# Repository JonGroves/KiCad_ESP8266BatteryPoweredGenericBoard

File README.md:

A generic ESP8266 board that allows for standard features, including programming, programming and reset buttons, USB connection (Power only), and breakout of pins.  ESP8266 is on it's own breakout board, and wide lcd screen breakout is provided for any size LCD (up to 24 pin spacings).

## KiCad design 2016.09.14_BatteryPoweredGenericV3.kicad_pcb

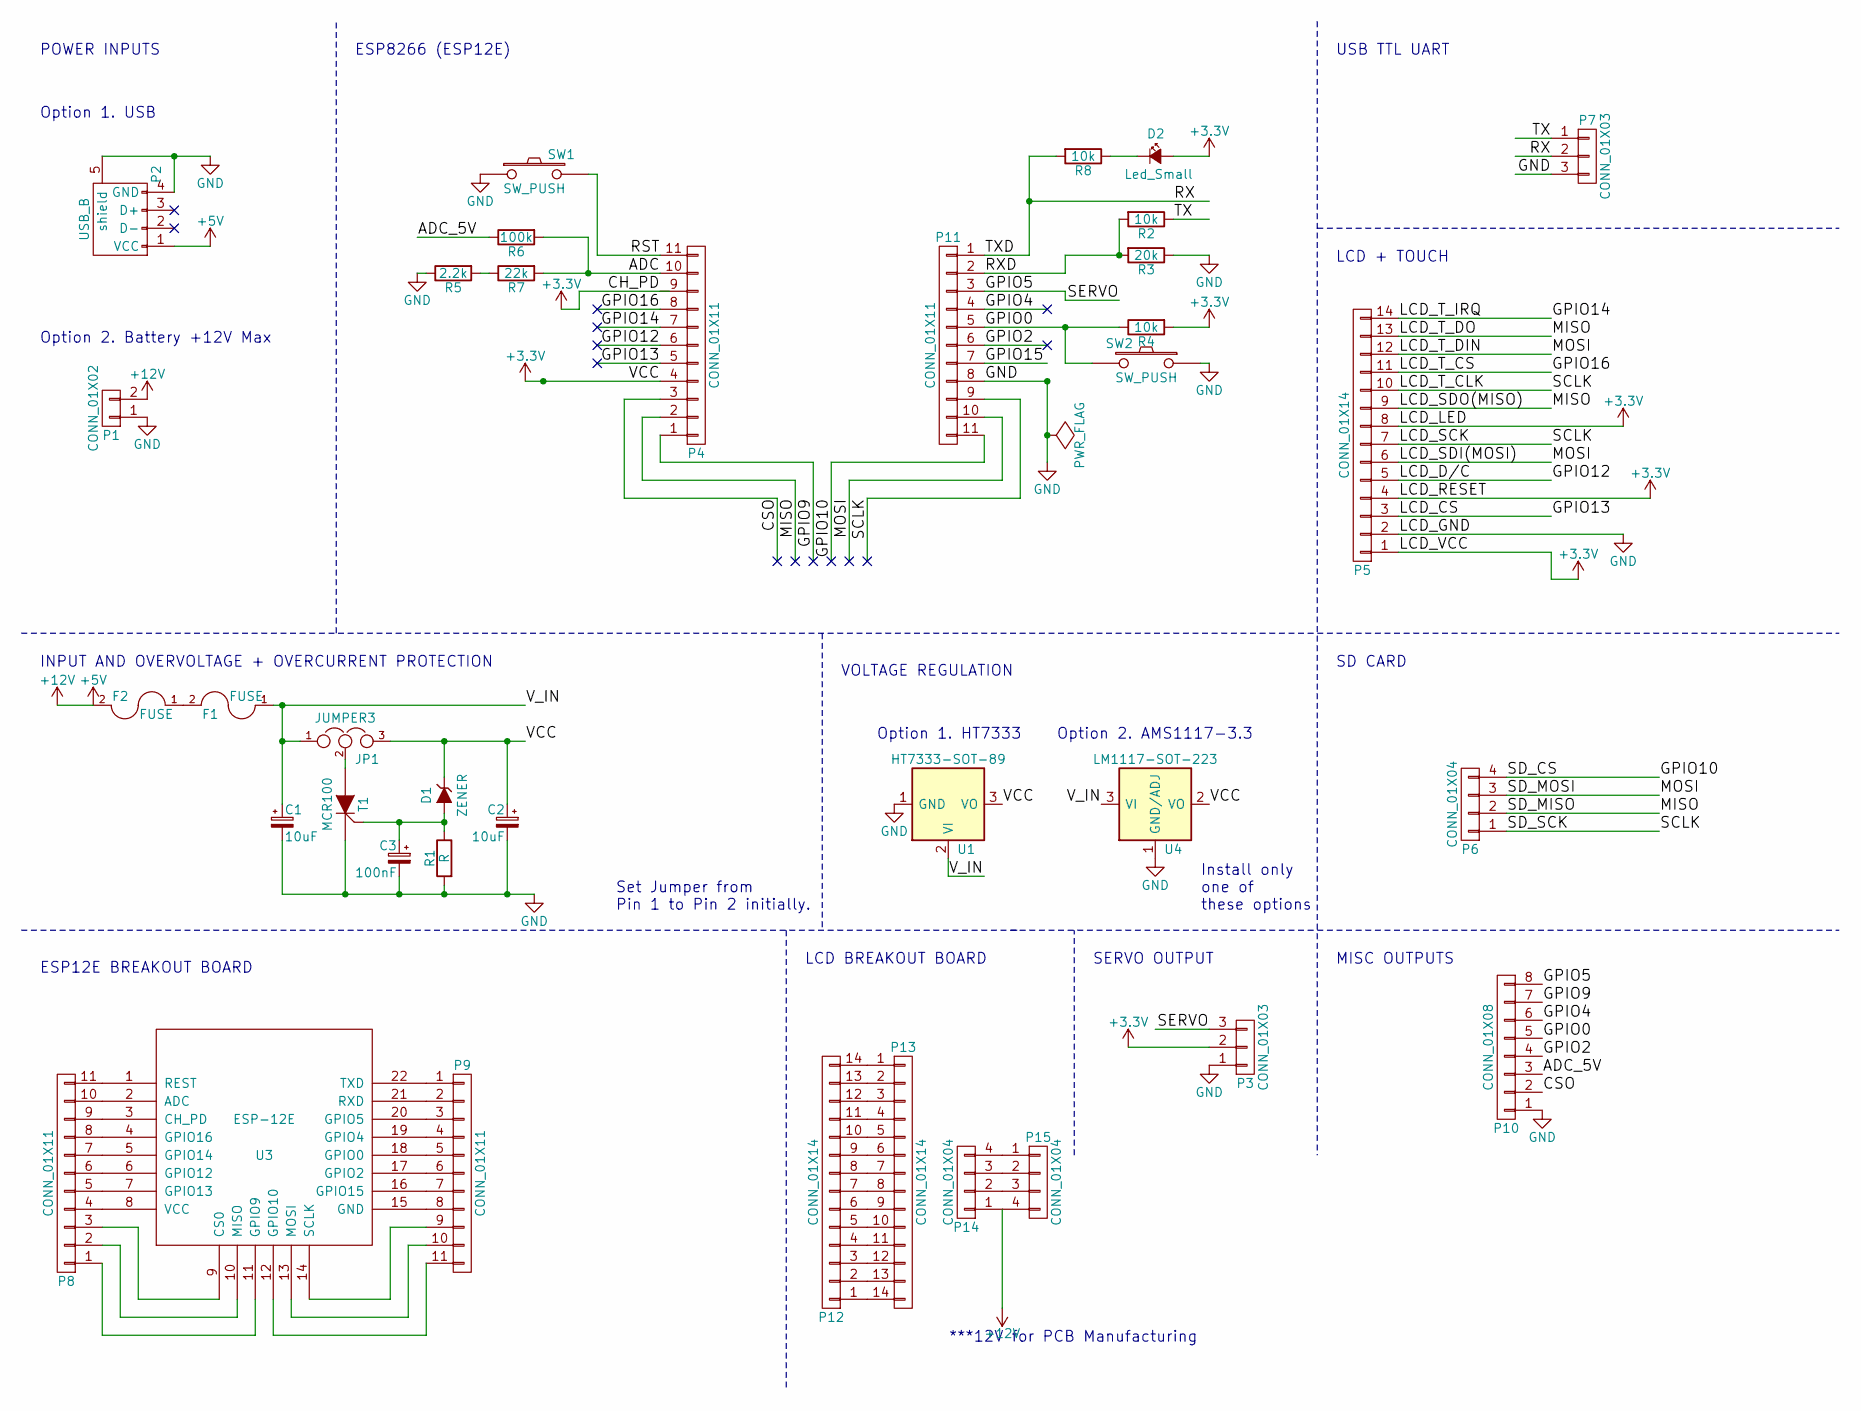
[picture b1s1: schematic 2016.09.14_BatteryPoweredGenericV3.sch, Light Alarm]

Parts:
C1, C2: 10uF; R_0805_HandSoldering
C3: 100nF; R_0805_HandSoldering
D1: ZENER; SOD-123
D2: Led_Small; LED_0603
F1: FUSE; R_1812_HandSoldering
F2: FUSE; Fuseholder5x20_horiz_open_Schurter_0031_8201
JP1: JUMPER3; R_1206_Junction
P1: CONN_01X02; Socket_Strip_Straight_1x02
P2: USB_B; USB_Mini-B
P3, P7: CONN_01X03; Socket_Strip_Straight_1x03
P4, P11: CONN_01X11; Socket_Strip_Straight_1x11
P5, P12: CONN_01X14; Socket_Strip_Straight_1x14
P6, P15: CONN_01X04; Socket_Strip_Straight_1x04
P8, P9: CONN_01X11; Pin_Header_Straight_1x11
P10: CONN_01X08; Socket_Strip_Straight_1x08
P13: CONN_01X14; Pin_Header_Straight_1x14
P14: CONN_01X04; Pin_Header_Straight_1x04
R1: R; R_0805_HandSoldering
R2, R4, R8: 10k; R_0805_HandSoldering
R3: 20k; R_0805_HandSoldering
R5: 2.2k; R_0805_HandSoldering
R6: 100k; R_0805_HandSoldering
R7: 22k; R_0805_HandSoldering
SW1, SW2: SW_PUSH; SW_SPST_EVPBF
T1: MCR100; TO-92_Inline_Narrow_Oval
U1: HT7333-SOT-89; SOT89-3_Housing_Handsoldering
U3: ESP-12E; Esp8266_PinsOnly
U4: LM1117-SOT-223; SOT-223

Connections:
+3V3: C2.1, D1.1 (K), D2.2 (A), JP1.3, P3.2, P4.4, P4.9, P5.1, P5.4, P5.8, R4.2, U1.3 (VO), U4.2 (VO)
+12V: F2.2, P1.2, P2.1 (VCC), P14.1, P15.4
/ADC: P4.10, R6.2, R7.2
/ADC_5V: P10.3, R6.1
/CSO: P4.3, P10.2
/GPIO0: P10.5, P11.5, R4.1, SW2.2
/GPIO2: P10.4, P11.6
/GPIO4: P10.6, P11.4
/GPIO5: P3.3, P10.8, P11.3
/GPIO9: P4.1, P10.7
/GPIO10: P6.4, P11.11
/GPIO12: P4.6, P5.5
/GPIO13: P4.5, P5.3
/GPIO14: P4.7, P5.14
/GPIO16: P4.8, P5.11
/LCD_SCK: P5.7, P5.10, P6.1, P11.9
/LCD_SDI(MOSI): P5.6, P5.12, P6.3, P11.10
/LCD_SDO(MISO): P4.2, P5.9, P5.13, P6.2
/RST: P4.11, SW1.2
/RX: P7.2, P11.1, R8.2
/RXD: P11.2, R2.2, R3.2
/TX: P7.1, R2.1
/V_IN: C1.1, F1.1, JP1.1, U1.2 (VI), U4.3 (VI)
GND: C1.2, C2.2, C3.2, P1.1, P2.4 (GND), P2.5 (shield), P3.1, P5.2, P7.3, P10.1, P11.8, R1.2, R3.1, R5.1, SW1.1, SW2.1, T1.1 (K), U1.1 (GND), U4.1 (GND/ADJ)
unnamed: C3.1, D1.2 (A), R1.1, T1.2 (G)
unnamed: D2.1 (K), R8.1
unnamed: F1.2, F2.1
unnamed: JP1.2, T1.3 (A)
unnamed: P8.1, U3.11 (GPIO9)
unnamed: P8.2, U3.10 (MISO)
unnamed: P8.3, U3.9 (CS0)
unnamed: P8.4, U3.8 (VCC)
unnamed: P8.5, U3.7 (GPIO13)
unnamed: P8.6, U3.6 (GPIO12)
unnamed: P8.7, U3.5 (GPIO14)
unnamed: P8.8, U3.4 (GPIO16)
unnamed: P8.9, U3.3 (CH_PD)
unnamed: P8.10, U3.2 (ADC)
unnamed: P8.11, U3.1 (REST)
unnamed: P9.1, U3.22 (TXD)
unnamed: P9.2, U3.21 (RXD)
unnamed: P9.3, U3.20 (GPIO5)
unnamed: P9.4, U3.19 (GPIO4)
unnamed: P9.5, U3.18 (GPIO0)
unnamed: P9.6, U3.17 (GPIO2)
unnamed: P9.7, U3.16 (GPIO15)
unnamed: P9.8, U3.15 (GND)
unnamed: P9.9, U3.14 (SCLK)
unnamed: P9.10, U3.13 (MOSI)
unnamed: P9.11, U3.12 (GPIO10)
unnamed: P12.1, P13.14
unnamed: P12.2, P13.13
unnamed: P12.3, P13.12
unnamed: P12.4, P13.11
unnamed: P12.5, P13.10
unnamed: P12.6, P13.9
unnamed: P12.7, P13.8
unnamed: P12.8, P13.7
unnamed: P12.9, P13.6
unnamed: P12.10, P13.5
unnamed: P12.11, P13.4
unnamed: P12.12, P13.3
unnamed: P12.13, P13.2
unnamed: P12.14, P13.1
unnamed 65: P14.2, P15.3; also elsewhere on the board
unnamed 66: P14.3, P15.2; also elsewhere on the board
unnamed 67: P14.4, P15.1; also elsewhere on the board
unnamed: R5.2, R7.1

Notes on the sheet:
USB TTL UART
POWER INPUTS
INPUT AND OVERVOLTAGE + OVERCURRENT PROTECTION
SERVO OUTPUT
LCD + TOUCH
SD CARD
MISC OUTPUTS
ESP8266 (ESP12E)
Option 1. USB
Option 2. Battery +12V Max
ESP12E BREAKOUT BOARD
Option 1. HT7333
Option 2. AMS1117-3.3
VOLTAGE REGULATION
LCD BREAKOUT BOARD
Set Jumper from Pin 1 to Pin 2 initially.
Install only one of these options
***12V for PCB Manufacturing

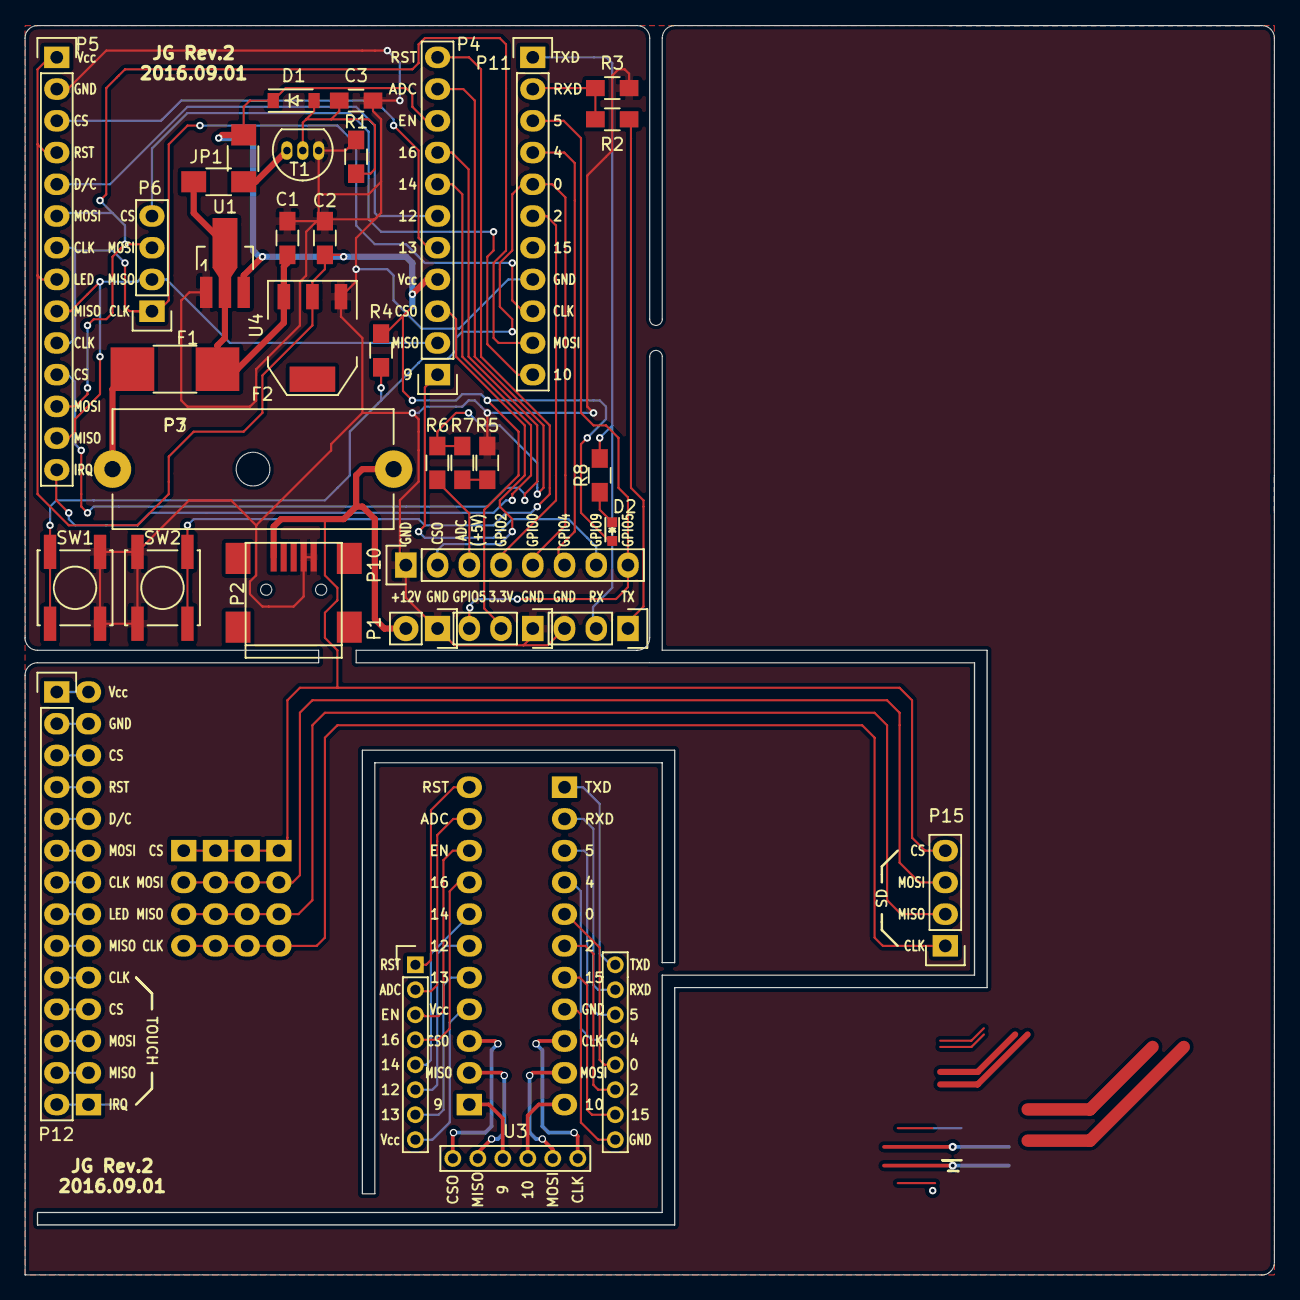
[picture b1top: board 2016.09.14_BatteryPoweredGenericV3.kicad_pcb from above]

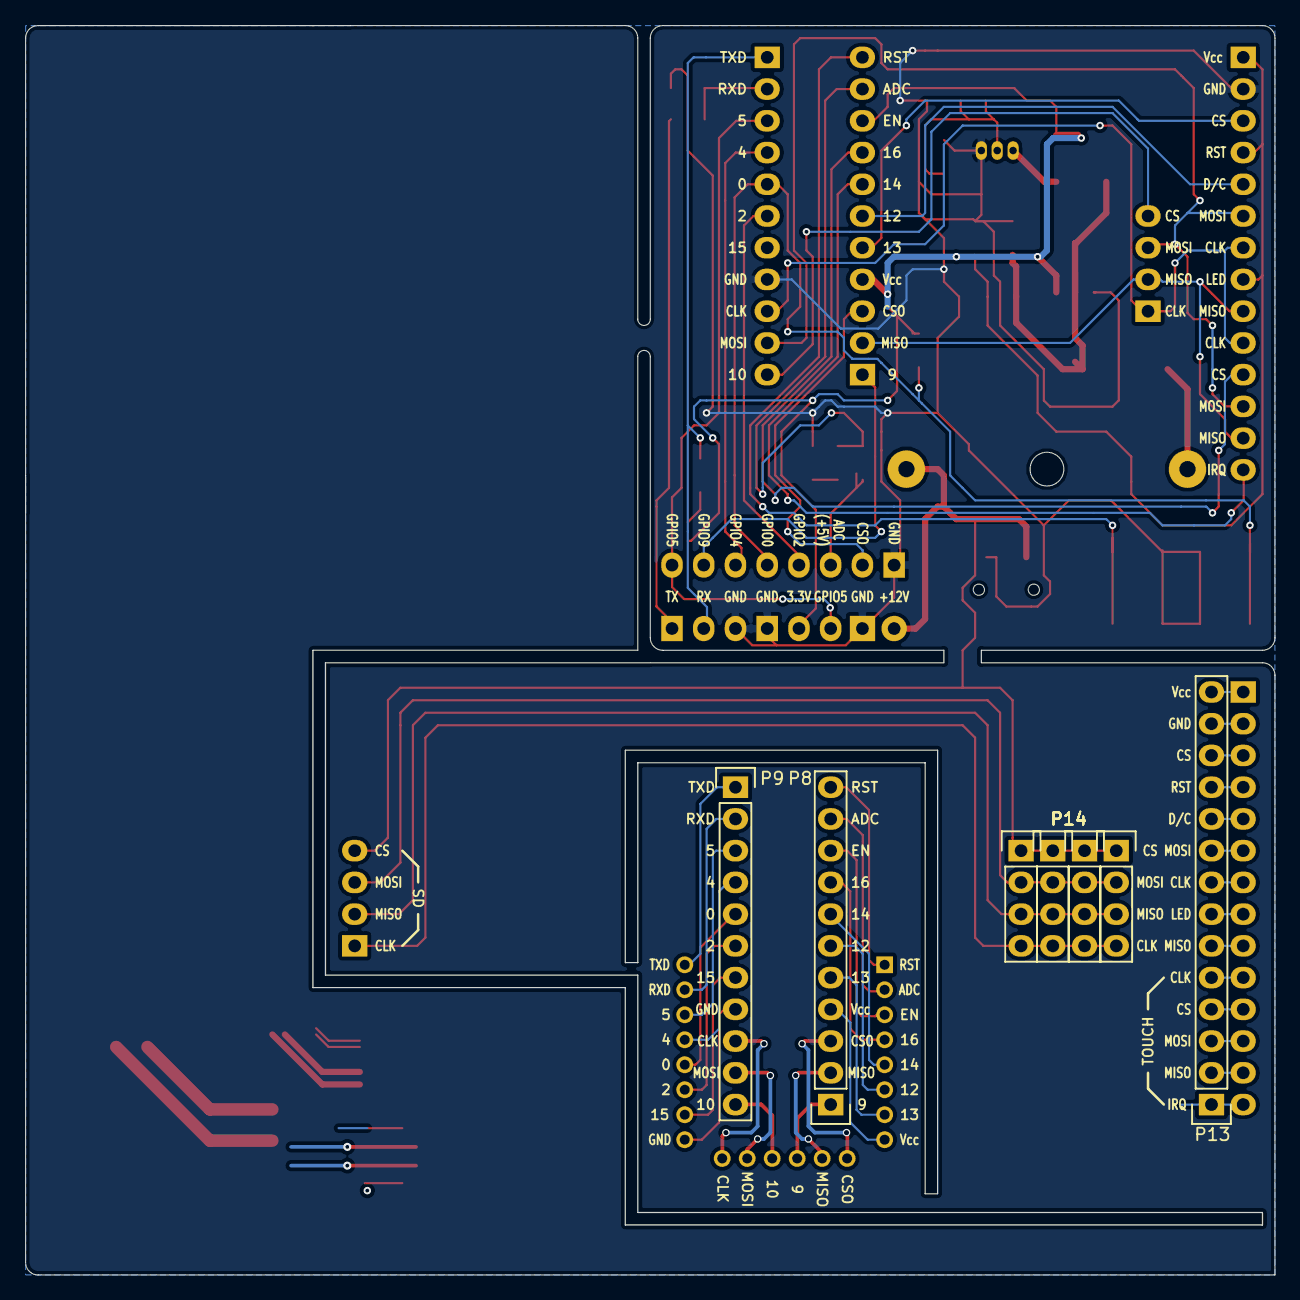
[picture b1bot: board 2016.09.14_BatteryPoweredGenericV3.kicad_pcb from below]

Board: 2 copper layers, 100.0 x 100.0 mm, 40 parts (7 on the bottom side), 69 nets.

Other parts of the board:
P14#2, P14#3, P14#4: CONN_01X04; Pin_Header_Straight_1x04

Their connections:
unnamed: P14#2.1, P14#3.1, P14#4.1
unnamed 65: P14#2.2, P14#3.2, P14#4.2; also elsewhere on the board
unnamed 66: P14#2.3, P14#3.3, P14#4.3; also elsewhere on the board
unnamed 67: P14#2.4, P14#3.4, P14#4.4; also elsewhere on the board

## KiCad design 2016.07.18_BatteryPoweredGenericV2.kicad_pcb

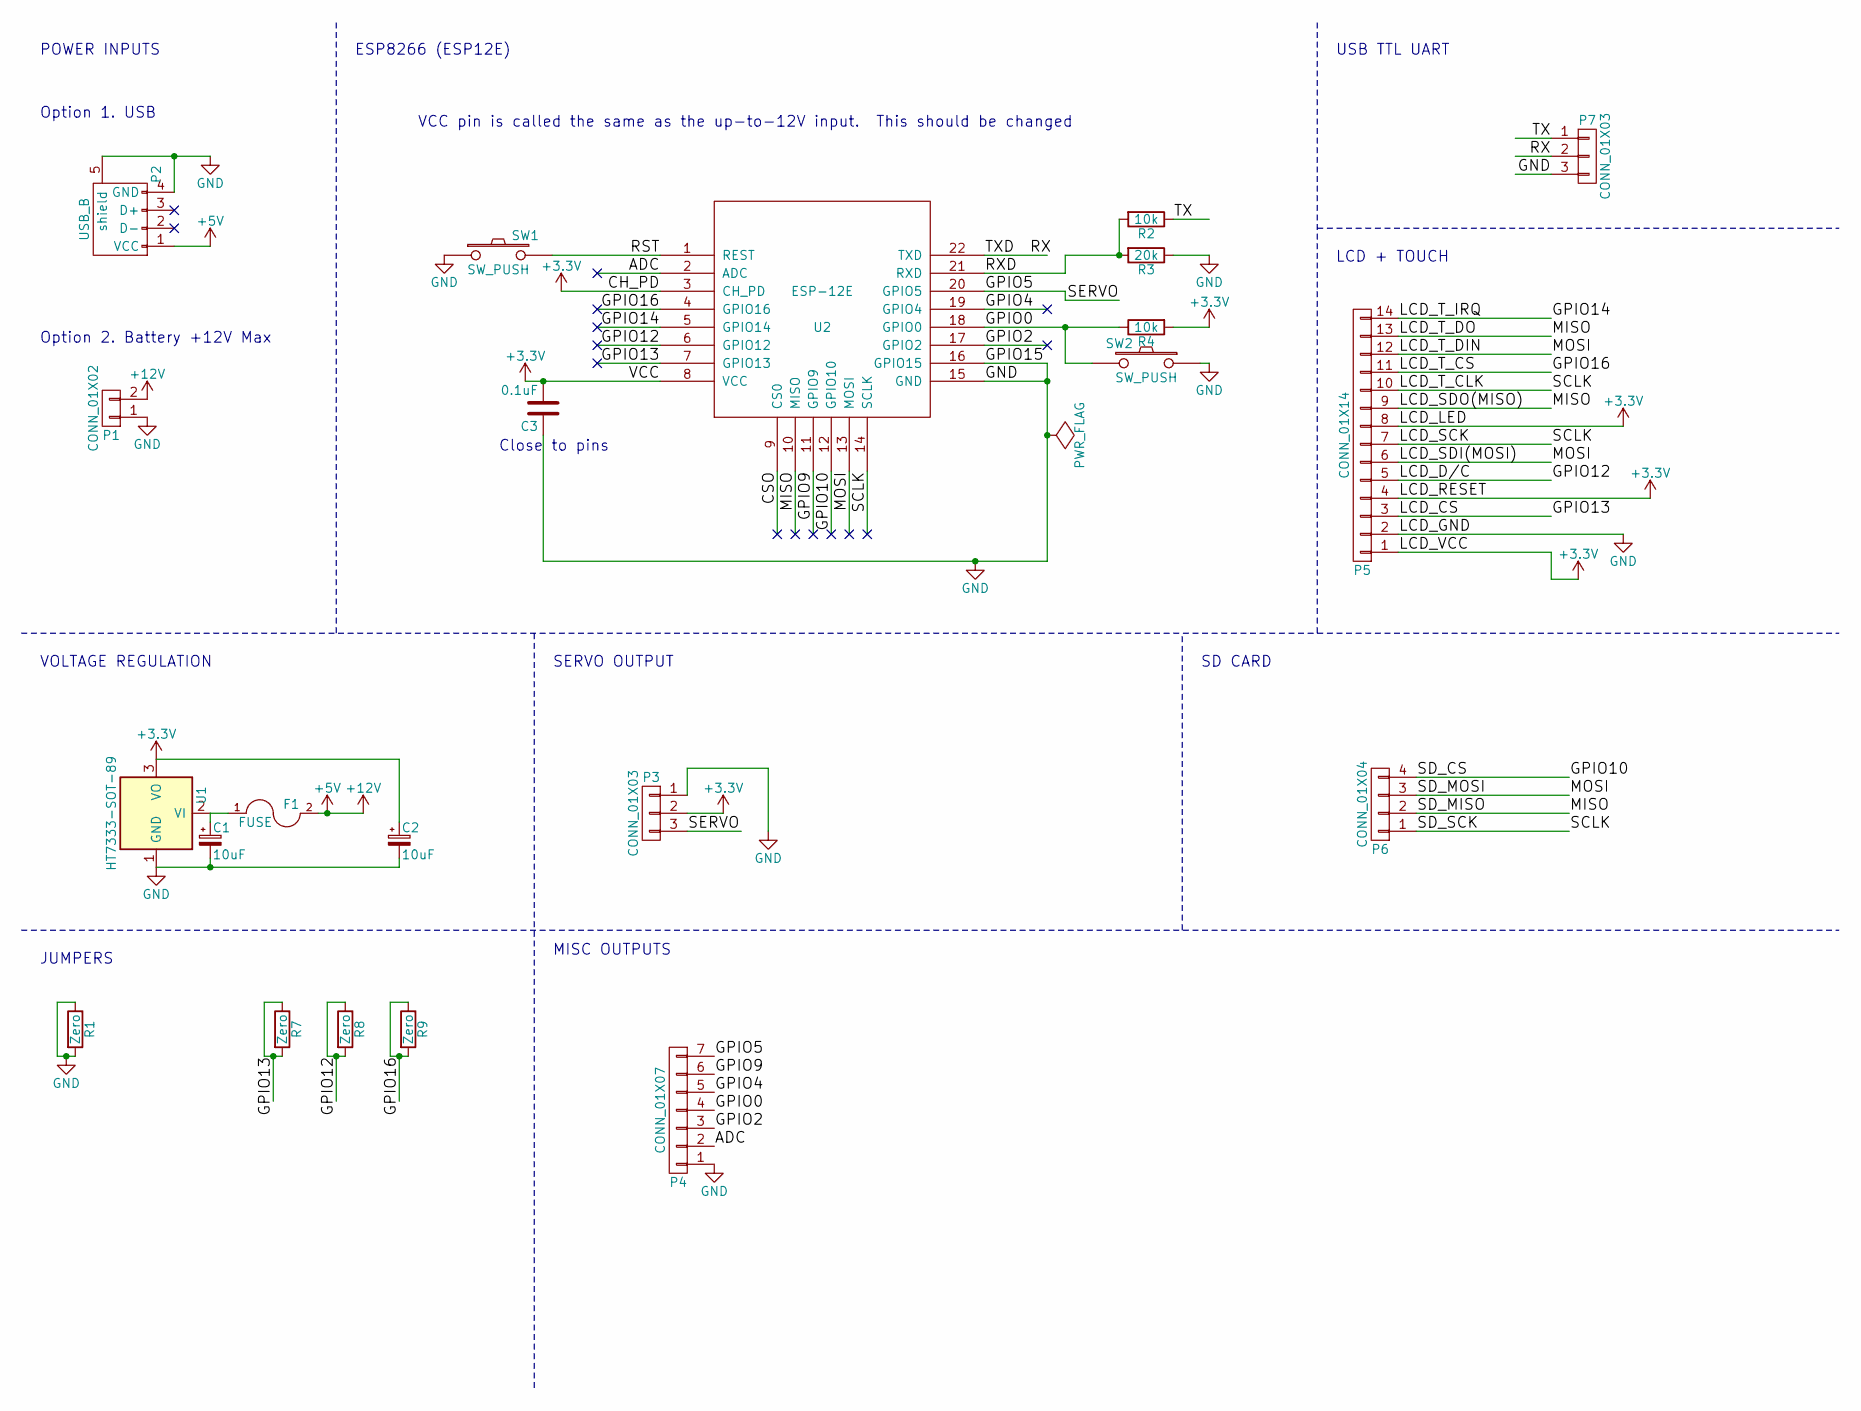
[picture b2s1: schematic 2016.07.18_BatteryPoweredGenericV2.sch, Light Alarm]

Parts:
C1, C2: 10uF; R_0805_HandSoldering
C3: 0.1uF; R_0805_HandSoldering
F1: FUSE; R_1812_HandSoldering
P1: CONN_01X02; Pin_Header_Angled_1x02
P2: USB_B; USB_Mini-B
P3, P7: CONN_01X03; Pin_Header_Angled_1x03
P4: CONN_01X07; Pin_Header_Angled_1x07
P5: CONN_01X14; Pin_Header_Angled_1x14
P6: CONN_01X04; Pin_Header_Angled_1x04
R1, R7, R8, R9: Zero; R_1206_HandSoldering
R2, R4: 10k; R_0805_HandSoldering
R3: 20k; R_0805_HandSoldering
SW1, SW2: SW_PUSH; SW_SPST_EVPBF
U1: HT7333-SOT-89; SOT89-3_Housing_Handsoldering
U2: ESP-12E

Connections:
+3V3: C2.1, C3.2, P3.2, P5.1, P5.4, P5.8, R4.2, U1.3 (VO), U2.3 (CH_PD), U2.8 (VCC)
+12V: F1.2, P1.2, P2.1 (VCC)
/ADC: P4.2, U2.2 (ADC)
/CSO: U2.9 (CS0)
/GPIO0: P4.4, R4.1, SW2.2, U2.18 (GPIO0)
/GPIO2: P4.3, U2.17 (GPIO2)
/GPIO4: P4.5, U2.19 (GPIO4)
/GPIO5: P3.3, P4.7, U2.20 (GPIO5)
/GPIO9: P4.6, U2.11 (GPIO9)
/GPIO10: P6.4, U2.12 (GPIO10)
/GPIO12: P5.5, R8.1, R8.2, U2.6 (GPIO12)
/GPIO13: P5.3, R7.1, R7.2, U2.7 (GPIO13)
/GPIO14: P5.14, U2.5 (GPIO14)
/GPIO16: P5.11, R9.1, R9.2, U2.4 (GPIO16)
/LCD_SCK: P5.7, P5.10, P6.1, U2.14 (SCLK)
/LCD_SDI(MOSI): P5.6, P5.12, P6.3, U2.13 (MOSI)
/LCD_SDO(MISO): P5.9, P5.13, P6.2, U2.10 (MISO)
/RST: SW1.2, U2.1 (REST)
/RX: P7.2, U2.22 (TXD)
/RXD: R2.2, R3.2, U2.21 (RXD)
/TX: P7.1, R2.1
GND: C1.2, C2.2, C3.1, P1.1, P2.4 (GND), P2.5 (shield), P3.1, P4.1, P5.2, P7.3, R1.1, R1.2, R3.1, SW1.1, SW2.1, U1.1 (GND), U2.15 (GND), U2.16 (GPIO15)
unnamed: C1.1, F1.1, U1.2 (VI)

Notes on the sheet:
USB TTL UART
Close to pins
VCC pin is called the same as the up-to-12V input. This should be changed
POWER INPUTS
VOLTAGE REGULATION
SERVO OUTPUT
LCD + TOUCH
SD CARD
MISC OUTPUTS
JUMPERS
ESP8266 (ESP12E)
Option 1. USB
Option 2. Battery +12V Max

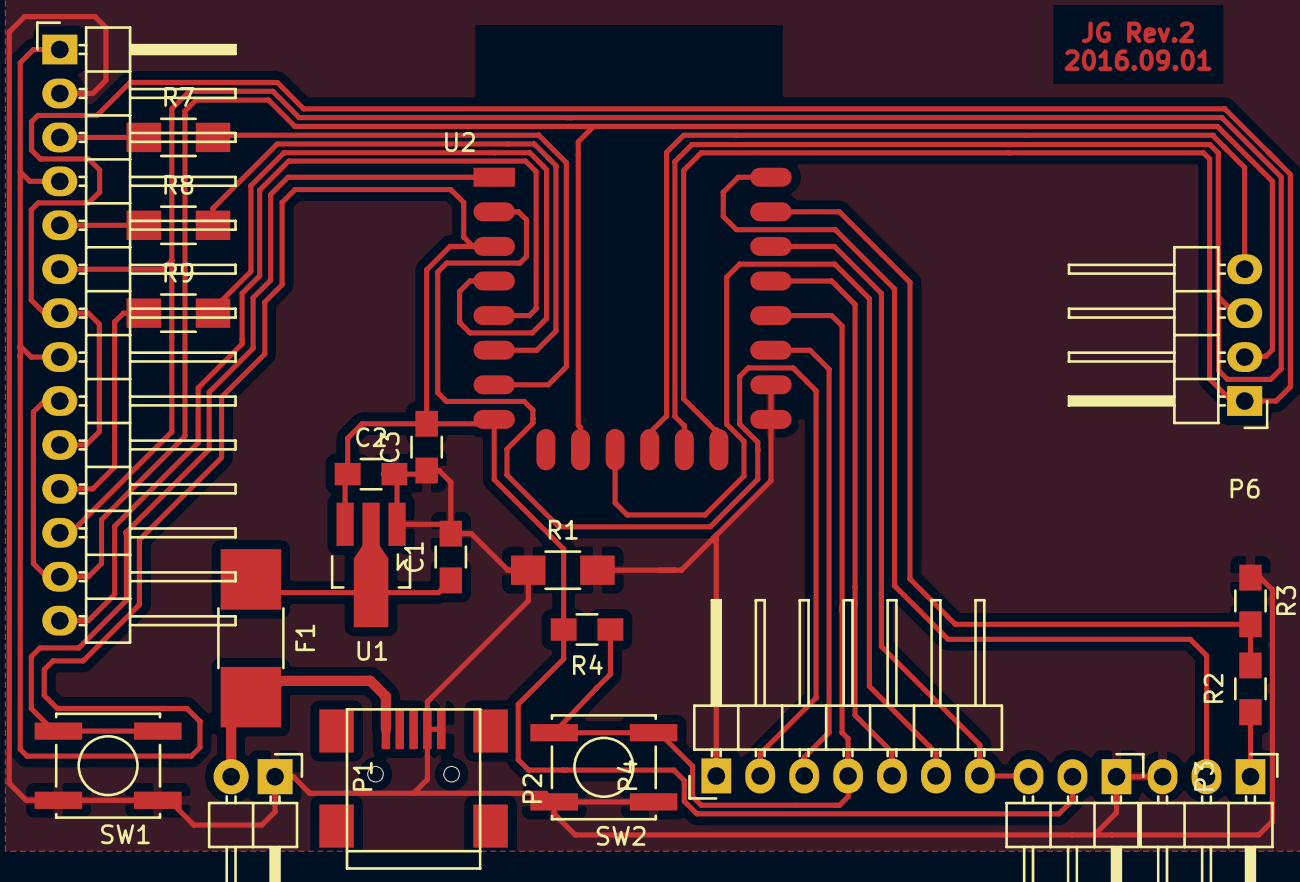
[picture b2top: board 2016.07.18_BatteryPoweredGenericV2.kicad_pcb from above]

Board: 2 copper layers, 22 parts (0 on the bottom side), 22 nets.

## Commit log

2016-07-19 Version 1.0
2016-07-19 Version 2.0
2016-09-15 Version 3.1
2016-09-15 Version 3.0
